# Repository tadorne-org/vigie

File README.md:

# Vigie

**English** · [Français](README.fr.md)

**The battery's lookout.** An always-alive energy node for small sailboats: a
board that measures the energy on board, sleeps at a few microamps and reports
from the bilge — all year round, with the battery switch off. A
[Tadorne](https://tadorne.org/) project.

## The problem

A battery runs flat while the boat is left alone. The usual causes — an
instrument still wired live, a converter that never sleeps, no charging — are
invisible from the quay.

## The approach

- **A single node stays alive.** Powered upstream of the battery switch, it
  measures the whole installation and reports; everything else on board can be
  switched off or dead.
- **A single source of truth.** All the current goes through one shunt, read
  with four wires in the negative bus. No charging current flows through the
  board.
- **A standby that does not drain.** A converter chosen for its quiescent
  current: what a conventional converter would draw in a month, Vigie draws in
  a year.
- **A network, not a box.** Vigie is the gateway of a small radio network:
  displays, attitude unit, wind sensor and a second current sensor can join as
  needed, and any of them can fail without taking the rest down.

## Status

**Vigie 1.0**: board designed, assembled, first tests passed. The KiCad
project is published under CERN-OHL-S v2 and the 1.0.0 firmware under GPL-3.0.
Eight milestones, from the bench to a season afloat:
[roadmap](https://vigie.tadorne.org/roadmap/) ·
[technical documentation](https://vigie.tadorne.org/documentation/) ·
[log](https://vigie.tadorne.org/log/).

## Repository contents

| Folder | Contents | Licence |
|---|---|---|
| [`pcb/`](pcb/) | Vigie 1.0 KiCad project: schematic, four-layer board, symbol library | [CERN-OHL-S v2](pcb/LICENSE) |
| [`firmware/`](firmware/) | 1.0.0 firmware of the energy node (ESP32, PlatformIO), bench gateway and tools (documentation in French) | [GPL-3.0](firmware/LICENSE) |
| [`mecanique/`](mecanique/) | TPU 95A sole and pad for an IP67 sealed enclosure: OpenSCAD source, STL files, Cura profiles (documentation in French) | to be specified |
| [`site/`](site/) | Hugo source of [vigie.tadorne.org](https://vigie.tadorne.org/) | content [CC BY-SA 4.0](site/LICENSE-CONTENT), templates [MIT](site/LICENSE) |

The content of `pcb/` (tag `v1.0`) is identical to the published, signed and
timestamped archive:
[`vigie-1.0-kicad.zip`](https://vigie.tadorne.org/files/vigie-1.0/vigie-1.0-kicad.zip),
[signature](https://vigie.tadorne.org/files/vigie-1.0/vigie-1.0-kicad.zip.asc),
[FreeTSA timestamp](https://vigie.tadorne.org/files/vigie-1.0/vigie-1.0-kicad.zip.tsr).

## Authenticity

Commits and published files are signed with the Tadorne key
(`5420 08E3 53EC A628 B4D6  ACAD 8C03 243A FF69 5BF7`); every commit is
timestamped by FreeTSA (RFC 3161), the token stored in the Git notes
`refs/notes/freetsa`. Verification: <https://tadorne.org/verify/>.

```sh
git fetch origin refs/notes/freetsa:refs/notes/freetsa
git notes --ref freetsa show HEAD
```

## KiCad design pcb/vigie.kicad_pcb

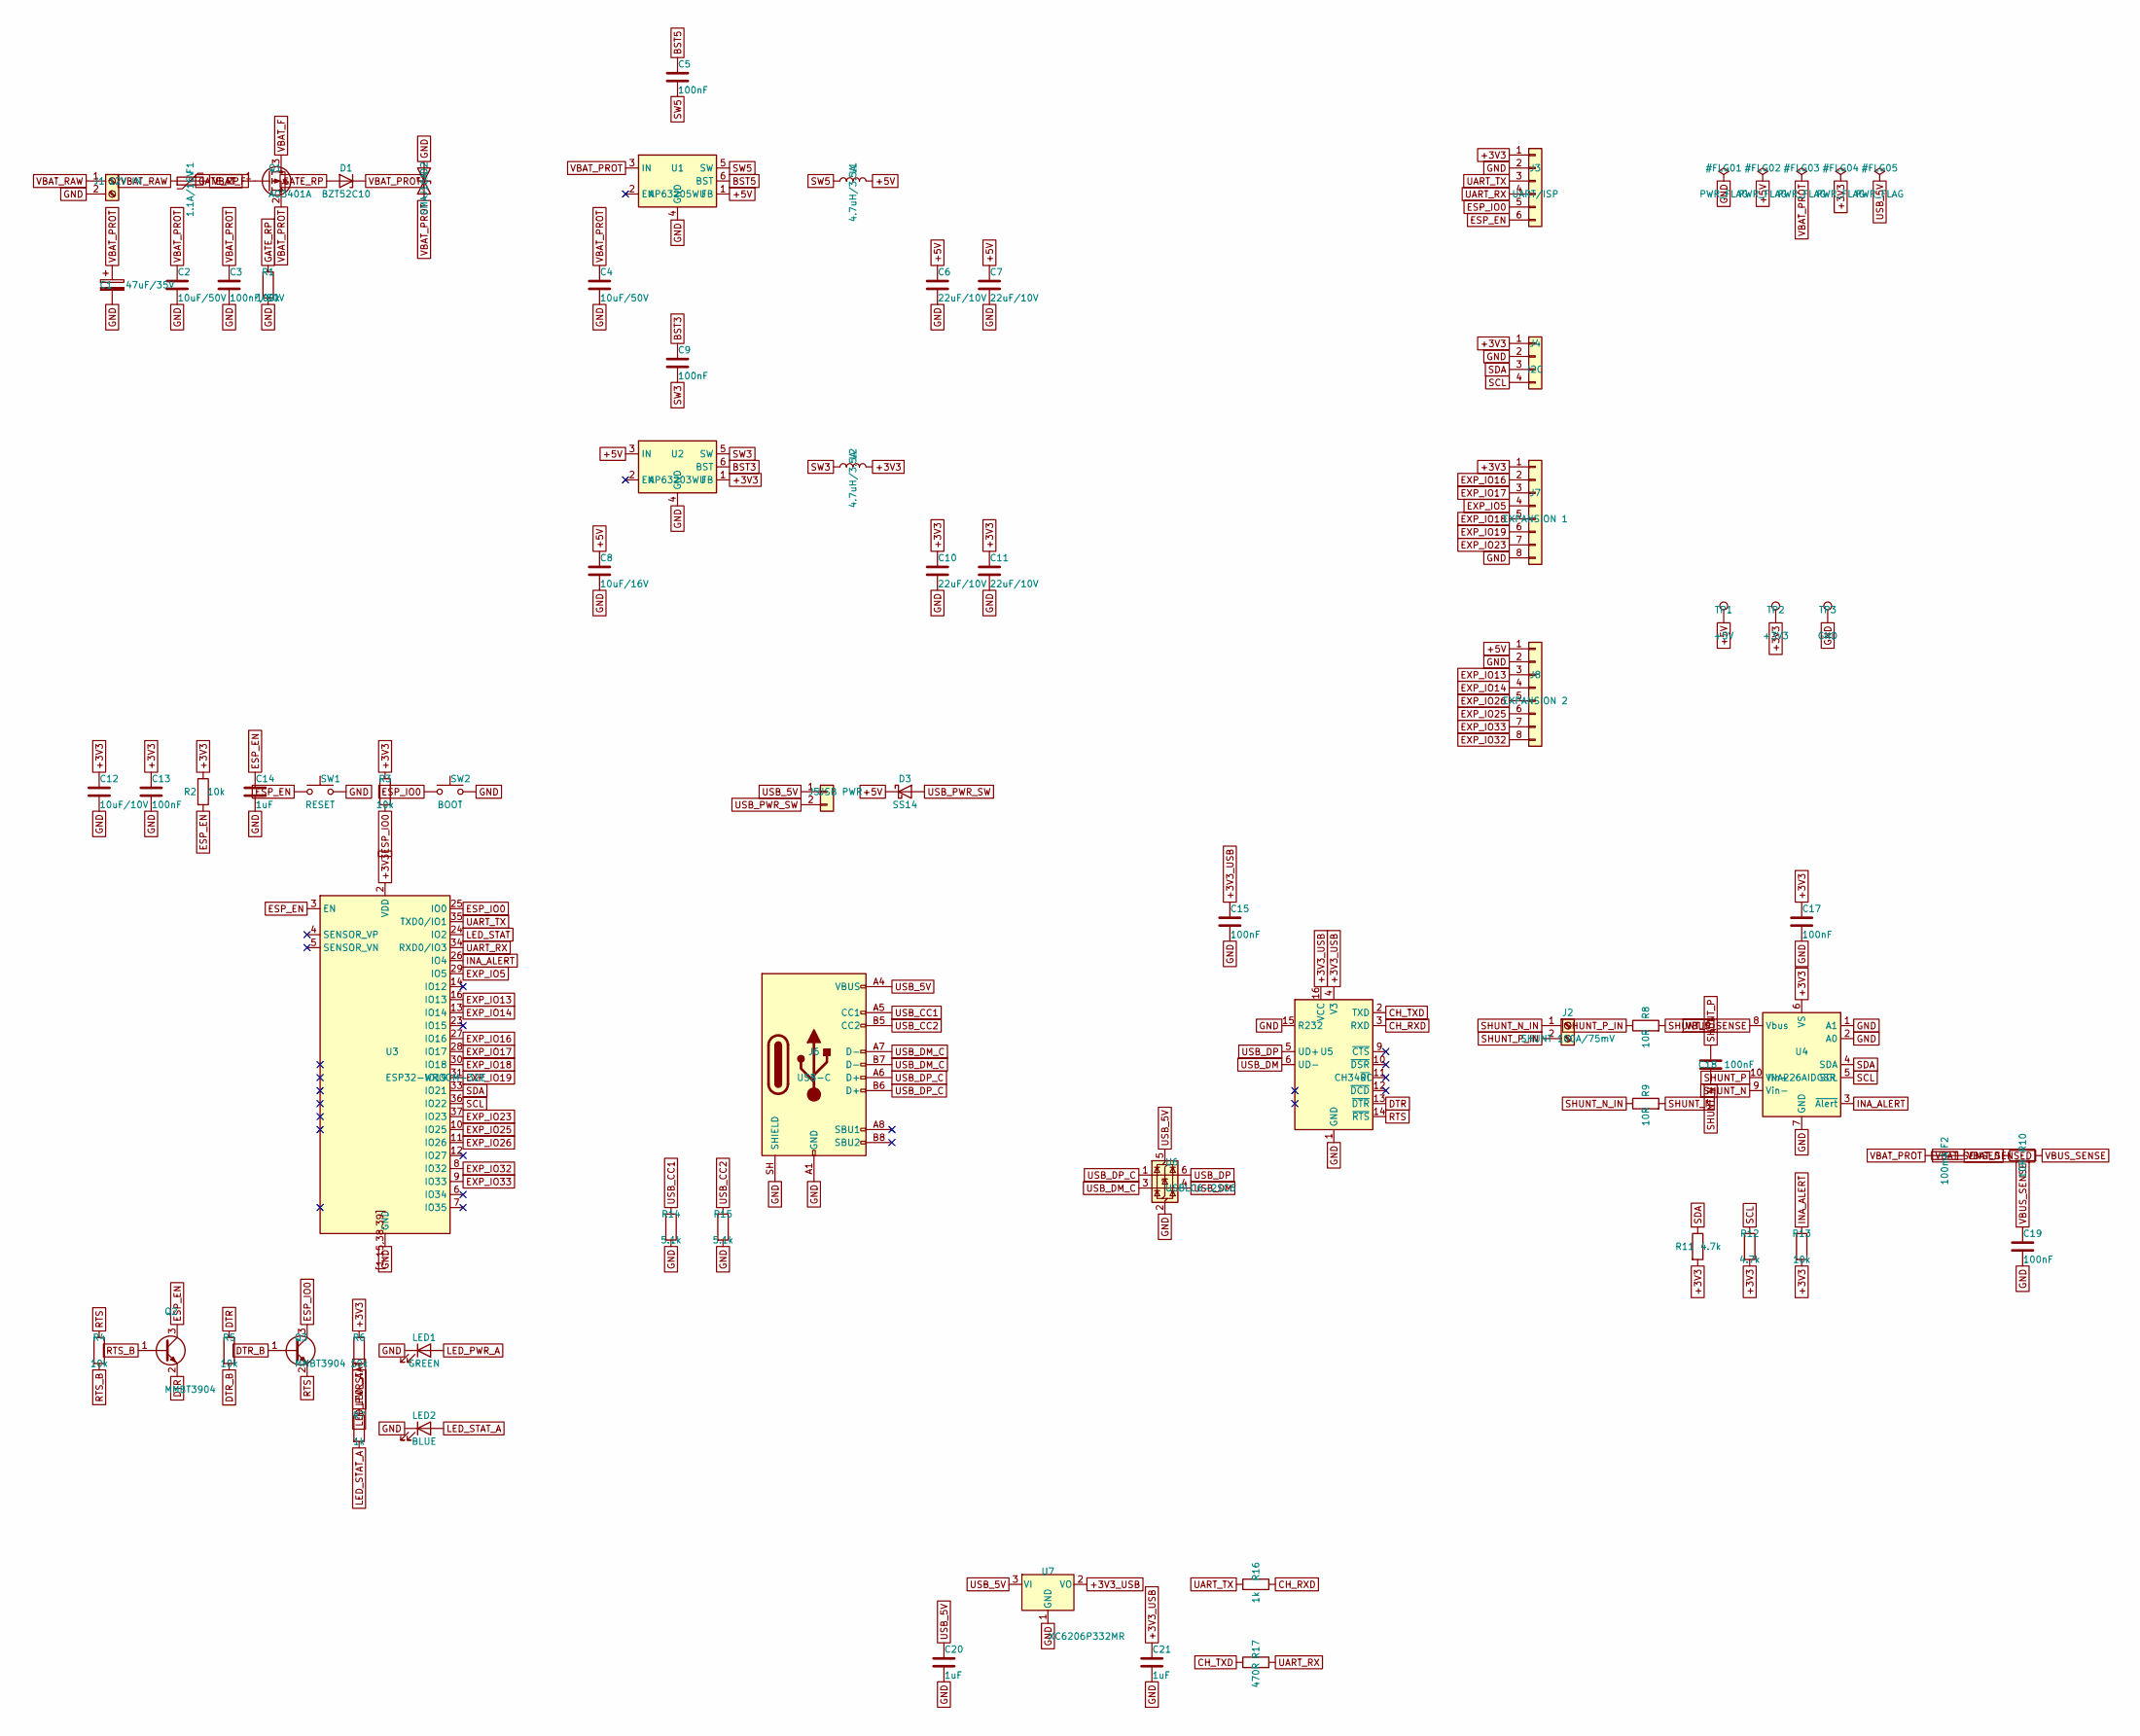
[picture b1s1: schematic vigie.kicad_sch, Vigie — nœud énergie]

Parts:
C1: 47uF/35V; CP_Elec_6.3x7.7
C2, C4: 10uF/50V; C_1210_3225Metric
C3: 100nF/50V; C_0603_1608Metric
C5, C9, C13, C15, C17, C18, C19: 100nF; C_0603_1608Metric
C6, C7, C10, C11: 22uF/10V; C_0805_2012Metric
C8: 10uF/16V; C_1206_3216Metric
C12: 10uF/10V; C_0805_2012Metric
C14, C20, C21: 1uF; C_0603_1608Metric
D1: BZT52C10; D_SOD-123
D2: SMAJ16A; D_SMA
D3: SS14; D_SMA
F1: 1.1A/16V; Fuse_1812_4532Metric
F2: 100mA; Fuse_1206_3216Metric
J1: 12V IN; TerminalBlock_Phoenix_MKDS-1,5-2-5.08_1x02_P5.08mm_Horizont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
J2: SHUNT 100A/75mV; TerminalBlock_Phoenix_PT-1,5-2-3.5-H_1x02_P3.50mm_Horizontal
J3: UART/ISP; PinHeader_1x06_P2.54mm_Vertical
J4: I2C; PinHeader_1x04_P2.54mm_Vertical
J5: USB PWR; PinHeader_1x02_P2.54mm_Vertical
J6: USB-C; USB_C_Receptacle_HRO_TYPE-C-31-M-12
J7: EXPANSION 1; PinHeader_1x08_P2.54mm_Vertical
J8: EXPANSION 2; PinHeader_1x08_P2.54mm_Vertical
L1, L2: 4.7uH/3.5A; L_Bourns_SRN6045TA
LED1: GREEN; LED_0805_2012Metric
LED2: BLUE; LED_0805_2012Metric
Q1: AO3401A; SOT-23
Q2, Q3: MMBT3904; SOT-23
R1: 100k; R_0603_1608Metric
R2, R3, R4, R5, R6, R13: 10k; R_0603_1608Metric
R7, R16: 1k; R_0603_1608Metric
R8, R9, R10: 10R; R_0603_1608Metric
R11, R12: 4.7k; R_0603_1608Metric
R14, R15: 5.1k; R_0603_1608Metric
R17: 470R; R_0603_1608Metric
SW1: RESET; SW_SPST_B3U-1000P
SW2: BOOT; SW_SPST_B3U-1000P
TP1: +5V; TestPoint_Pad_D1.5mm
TP2: +3V3; TestPoint_Pad_D1.5mm
TP3: GND; TestPoint_Pad_D1.5mm
U1: AP63205WU; TSOT-23-6
U2: AP63203WU; TSOT-23-6
U3: ESP32-WROOM-32E
U4: INA226AIDGSR; TSSOP-10_3x3mm_P0.5mm
U5: CH340C; SOIC-16_3.9x9.9mm_P1.27mm
U6: USBLC6-2SC6; SOT-23-6
U7: XC6206P332MR; SOT-23

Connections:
+3V3: C10.1, C11.1, C12.1, C13.1, C17.1, J3.1, J4.1, J7.1, L2.2, R2.1, R3.1, R6.1, R11.2, R12.2, R13.2, TP2.1, U2.1 (FB), U3.2 (VDD), U4.6 (VS)
+3V3_USB: C15.1, C21.1, U5.4 (V3), U5.16 (VCC), U7.2 (VO)
+5V: C6.1, C7.1, C8.1, D3.1 (K), J8.1, L1.2, TP1.1, U1.1 (FB), U2.3 (IN)
BST3: C9.1, U2.6 (BST)
BST5: C5.1, U1.6 (BST)
CH_RXD: R16.2, U5.3 (RXD)
CH_TXD: R17.1, U5.2 (TXD)
DTR: Q2.2 (E), R5.1, U5.13 (~DTR)
DTR_B: Q3.1 (B), R5.2
ESP_EN: C14.1, J3.6, Q2.3 (C), R2.2, SW1.1, U3.3 (EN)
ESP_IO0: J3.5, Q3.3 (C), R3.2, SW2.1, U3.25 (IO0)
EXP_IO5: J7.4, U3.29 (IO5)
EXP_IO13: J8.3, U3.16 (IO13)
EXP_IO14: J8.4, U3.13 (IO14)
EXP_IO16: J7.2, U3.27 (IO16)
EXP_IO17: J7.3, U3.28 (IO17)
EXP_IO18: J7.5, U3.30 (IO18)
EXP_IO19: J7.6, U3.31 (IO19)
EXP_IO23: J7.7, U3.37 (IO23)
EXP_IO25: J8.6, U3.10 (IO25)
EXP_IO26: J8.5, U3.11 (IO26)
EXP_IO32: J8.8, U3.8 (IO32)
EXP_IO33: J8.7, U3.9 (IO33)
GATE_RP: D1.2 (A), Q1.1 (G), R1.1
GND: C1.2, C2.2, C3.2, C4.2, C6.2, C7.2, C8.2, C10.2, C11.2, C12.2, C13.2, C14.2, C15.2, C17.2, C19.2, C20.2, C21.2, D2.2 (A2), J1.2, J3.2, J4.2, J6.A1 (GND), J6.A12 (GND), J6.B1 (GND), J6.B12 (GND), J6.SH (SHIELD), J7.8, J8.2, LED1.1 (K), LED2.1 (K), R1.2, R14.2, R15.2, SW1.2, SW2.2, TP3.1, U1.4 (GND), U2.4 (GND), U3.1, U3.15, U3.38, U3.39, U3.[1,15,38,39] (GND), U4.1 (A1), U4.2 (A0), U4.7 (GND), U5.1 (GND), U5.15 (R232), U6.2 (GND), U7.1 (GND)
INA_ALERT: R13.1, U3.26 (IO4), U4.3 (~Alert)
LED_PWR_A: LED1.2 (A), R6.2
LED_STAT: R7.1, U3.24 (IO2)
LED_STAT_A: LED2.2 (A), R7.2
RTS: Q3.2 (E), R4.1, U5.14 (~RTS)
RTS_B: Q2.1 (B), R4.2
SCL: J4.4, R12.1, U3.36 (IO22), U4.5 (SCL)
SDA: J4.3, R11.1, U3.33 (IO21), U4.4 (SDA)
SHUNT_N: C18.2, R9.2, U4.9 (Vin-)
SHUNT_N_IN: J2.1, R9.1
SHUNT_P: C18.1, R8.2, U4.10 (Vin+)
SHUNT_P_IN: J2.2, R8.1
SW3: C9.2, L2.1, U2.5 (SW)
SW5: C5.2, L1.1, U1.5 (SW)
UART_RX: J3.4, R17.2, U3.34 (RXD0/IO3)
UART_TX: J3.3, R16.1, U3.35 (TXD0/IO1)
USB_5V: C20.1, J5.1, J6.A4 (VBUS), J6.A9 (VBUS), J6.B4 (VBUS), J6.B9 (VBUS), U6.5 (VBUS), U7.3 (VI)
USB_CC1: J6.A5 (CC1), R14.1
USB_CC2: J6.B5 (CC2), R15.1
USB_DM: U5.6 (UD-), U6.4 (I/O2)
USB_DM_C: J6.A7 (D-), J6.B7 (D-), U6.3 (I/O2)
USB_DP: U5.5 (UD+), U6.6 (I/O1)
USB_DP_C: J6.A6 (D+), J6.B6 (D+), U6.1 (I/O1)
USB_PWR_SW: D3.2 (A), J5.2
VBAT_F: F1.2, Q1.3 (D)
VBAT_PROT: C1.1, C2.1, C3.1, C4.1, D1.1 (K), D2.1 (A1), F2.1, Q1.2 (S), U1.3 (IN)
VBAT_RAW: F1.1, J1.1
VBAT_SENSED: F2.2, R10.1
VBUS_SENSE: C19.1, R10.2, U4.8 (Vbus)

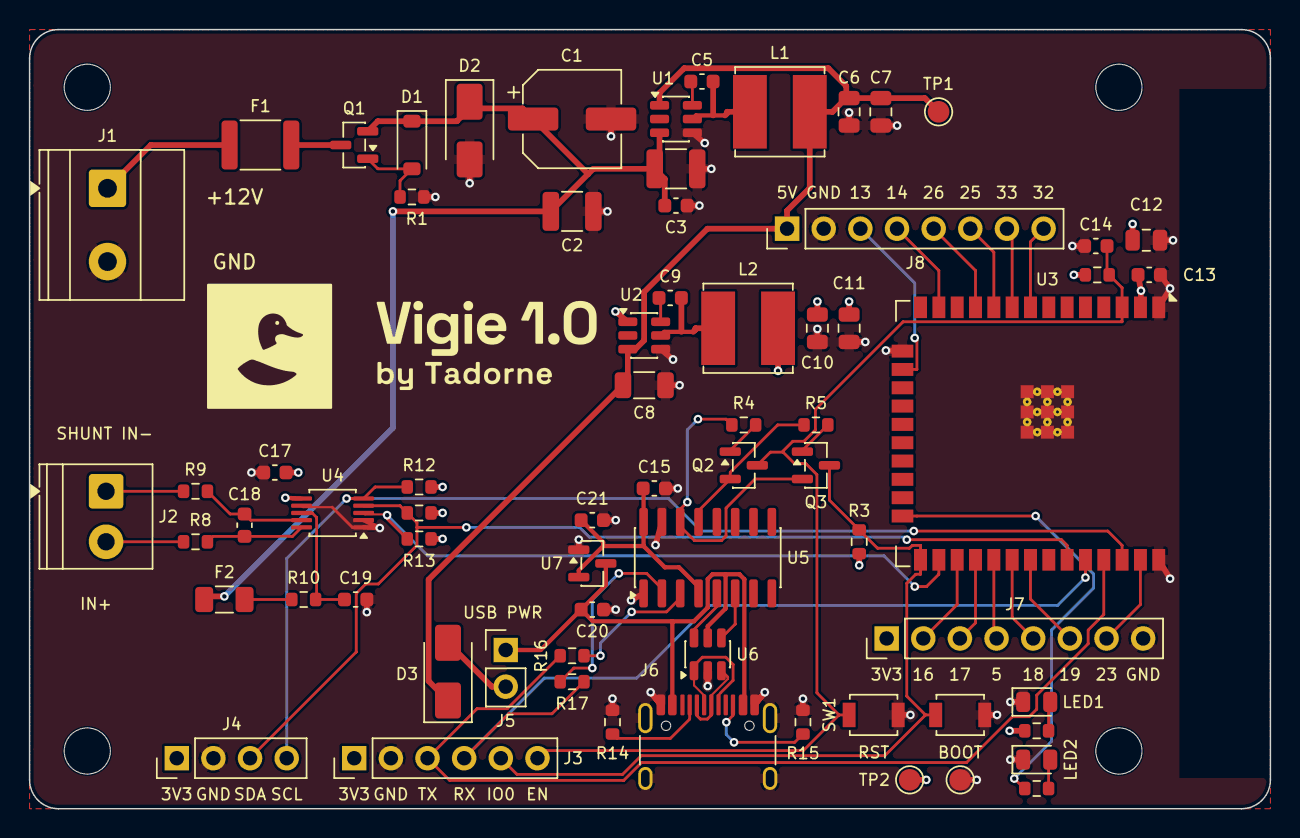
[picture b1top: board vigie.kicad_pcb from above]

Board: 4 copper layers, 86.0 x 54.0 mm, 74 parts (0 on the bottom side), 54 nets.

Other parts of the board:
H1, H2, H3, H4: M3; MountingHole_3.2mm_M3
LOGO1: vigie-silk
